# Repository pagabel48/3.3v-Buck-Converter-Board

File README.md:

# 3.3v Buck Converter Board

This board uses a buck converter to output regulated 3.3v from a 4s LiPo battery. It has been used to successfully power an Arduino Microcontroller.

## Schematic

## Routing

Since the board is only designed to handle 1A, .5mm traces were used. This makes soldering easier.

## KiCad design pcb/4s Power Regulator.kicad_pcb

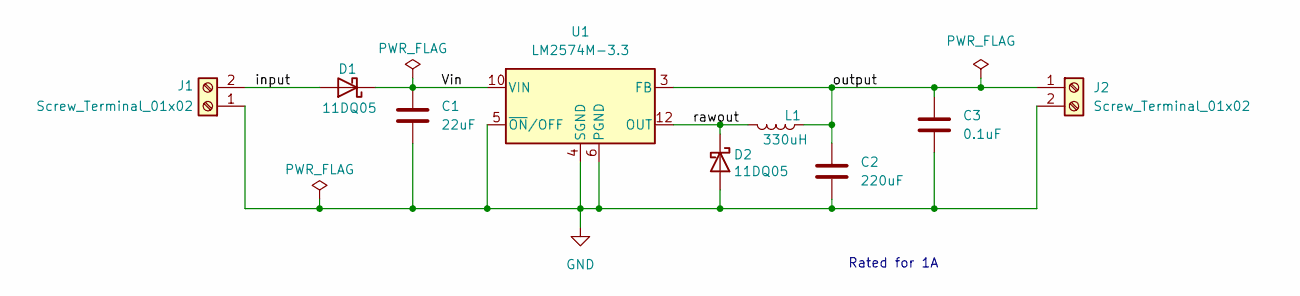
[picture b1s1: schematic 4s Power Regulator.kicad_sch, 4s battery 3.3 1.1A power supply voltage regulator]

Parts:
C1: 22uF; C_Radial_D5.0mm_H5.0mm_P2.00mm
C2: 220uF; C_Radial_D6.3mm_H11.0mm_P2.50mm
C3: 0.1uF; C_Disc_D3.0mm_W2.0mm_P2.50mm
D1, D2: 11DQ05; D_DO-41_SOD81_P7.62mm_Horizontal
J1, J2: Screw_Terminal_01x02; TerminalBlock_Phoenix_MKDS-1,5-2-5.08_1x02_P5.08mm_Horizont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
L1: 330uH; L_Axial_L5.3mm_D2.2mm_P7.62mm_Horizontal_Vishay_IM-1
U1: LM2574M-3.3; SOIC-14W_7.5x9mm_P1.27mm

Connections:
/Vin: C1.1, D1.1 (K), U1.10 (VIN)
/input: D1.2 (A), J1.2
/output: C2.1, C3.1, J2.1, L1.1, U1.3 (FB)
/rawout: D2.1 (K), L1.2, U1.12 (OUT)
GND: C1.2, C2.2, C3.2, D2.2 (A), J1.1, J2.2, U1.4 (SGND), U1.5 (~ON/OFF), U1.6 (PGND)

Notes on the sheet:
Rated for 1A

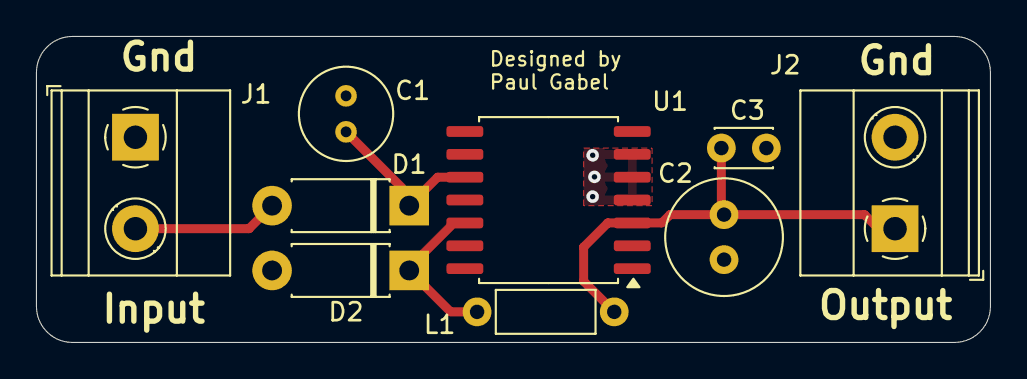
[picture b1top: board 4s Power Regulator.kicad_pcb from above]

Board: 2 copper layers, 53.0 x 17.0 mm, 9 parts (0 on the bottom side), 5 nets.

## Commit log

2025-07-09 :star: initial commit
